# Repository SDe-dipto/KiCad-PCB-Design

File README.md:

# KiCad-PCB-Design
This repository contains project designs of PCBs implemented using KiCad tool. 

## Example projects
1. 6SN7 dual triode vacuum tube
2. 10-channel equaliser
3. Circular LED board
4. LM324 operational amplifier-based filter

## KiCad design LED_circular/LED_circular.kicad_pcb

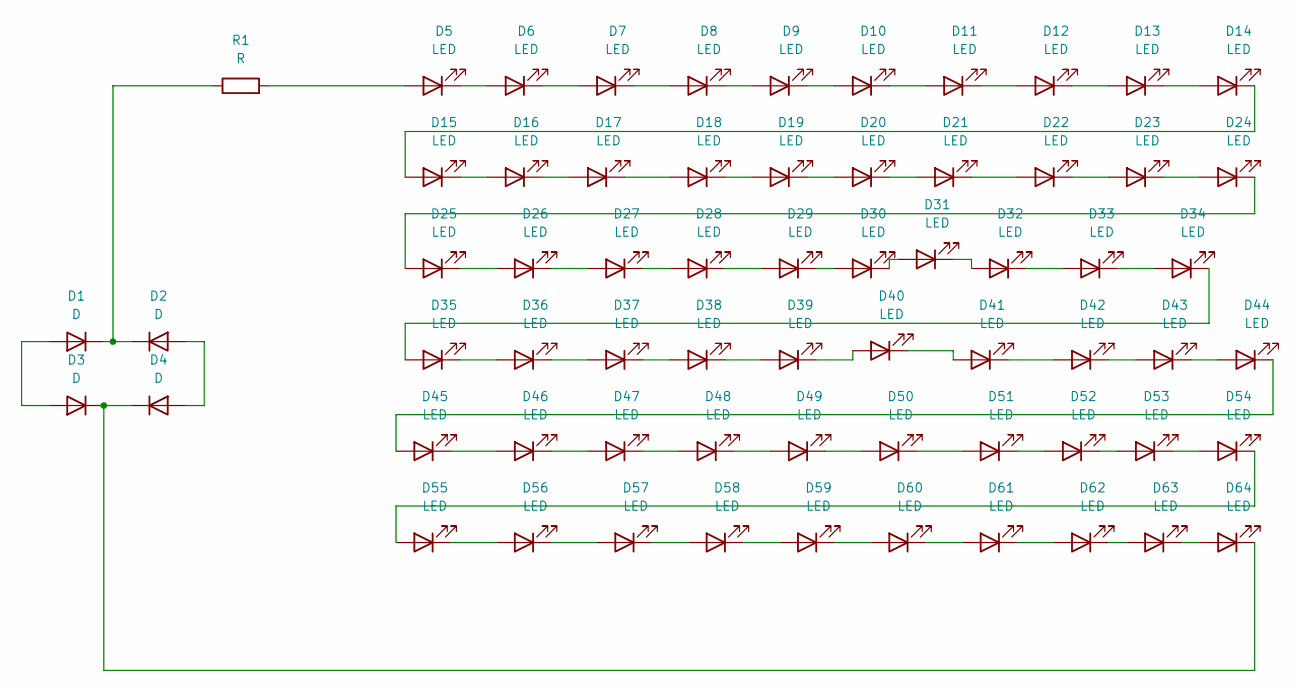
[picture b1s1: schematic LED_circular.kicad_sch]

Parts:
D1, D2, D3, D4: D; D_1206_3216Metric
D5, D6, D7, D8, D9, D10, D11, D12, D13, D14, D15, D16, D17, D18, D19, D20, D21, D22, D23, D24, D25, D26, D27, D28, D29, D30, D31, D32, D33, D34, D35, D36, D37, D38, D39, D40, D41, D42, D43, D44, D45, D46, D47, D48, D49, D50, D51, D52, D53, D54, D55, D56, D57, D58, D59, D60, D61, D62, D63, D64: LED; LED_1206_3216Metric
R1: R; R_1206_3216Metric

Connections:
unnamed: D1.2 (A), D3.2 (A)
unnamed: D1.1 (K), D2.1 (K), R1.1
unnamed: D2.2 (A), D4.2 (A)
unnamed: D3.1 (K), D4.1 (K), D64.1 (K)
unnamed: D5.2 (A), R1.2
unnamed: D5.1 (K), D6.2 (A)
unnamed: D6.1 (K), D7.2 (A)
unnamed: D7.1 (K), D8.2 (A)
unnamed: D8.1 (K), D9.2 (A)
unnamed: D9.1 (K), D10.2 (A)
unnamed: D10.1 (K), D11.2 (A)
unnamed: D11.1 (K), D12.2 (A)
unnamed: D12.1 (K), D13.2 (A)
unnamed: D13.1 (K), D14.2 (A)
unnamed: D14.1 (K), D15.2 (A)
unnamed: D15.1 (K), D16.2 (A)
unnamed: D16.1 (K), D17.2 (A)
unnamed: D17.1 (K), D18.2 (A)
unnamed: D18.1 (K), D19.2 (A)
unnamed: D19.1 (K), D20.2 (A)
unnamed: D20.1 (K), D21.2 (A)
unnamed: D21.1 (K), D22.2 (A)
unnamed: D22.1 (K), D23.2 (A)
unnamed: D23.1 (K), D24.2 (A)
unnamed: D24.1 (K), D25.2 (A)
unnamed: D25.1 (K), D26.2 (A)
unnamed: D26.1 (K), D27.2 (A)
unnamed: D27.1 (K), D28.2 (A)
unnamed: D28.1 (K), D29.2 (A)
unnamed: D29.1 (K), D30.2 (A)
unnamed: D30.1 (K), D31.2 (A)
unnamed: D31.1 (K), D32.2 (A)
unnamed: D32.1 (K), D33.2 (A)
unnamed: D33.1 (K), D34.2 (A)
unnamed: D34.1 (K), D35.2 (A)
unnamed: D35.1 (K), D36.2 (A)
unnamed: D36.1 (K), D37.2 (A)
unnamed: D37.1 (K), D38.2 (A)
unnamed: D38.1 (K), D39.2 (A)
unnamed: D39.1 (K), D40.2 (A)
unnamed: D40.1 (K), D41.2 (A)
unnamed: D41.1 (K), D42.2 (A)
unnamed: D42.1 (K), D43.2 (A)
unnamed: D43.1 (K), D44.2 (A)
unnamed: D44.1 (K), D45.2 (A)
unnamed: D45.1 (K), D46.2 (A)
unnamed: D46.1 (K), D47.2 (A)
unnamed: D47.1 (K), D48.2 (A)
unnamed: D48.1 (K), D49.2 (A)
unnamed: D49.1 (K), D50.2 (A)
unnamed: D50.1 (K), D51.2 (A)
unnamed: D51.1 (K), D52.2 (A)
unnamed: D52.1 (K), D53.2 (A)
unnamed: D53.1 (K), D54.2 (A)
unnamed: D54.1 (K), D55.2 (A)
unnamed: D55.1 (K), D56.2 (A)
unnamed: D56.1 (K), D57.2 (A)
unnamed: D57.1 (K), D58.2 (A)
unnamed: D58.1 (K), D59.2 (A)
unnamed: D59.1 (K), D60.2 (A)
unnamed: D60.1 (K), D61.2 (A)
unnamed: D61.1 (K), D62.2 (A)
unnamed: D62.1 (K), D63.2 (A)
unnamed: D63.1 (K), D64.2 (A)

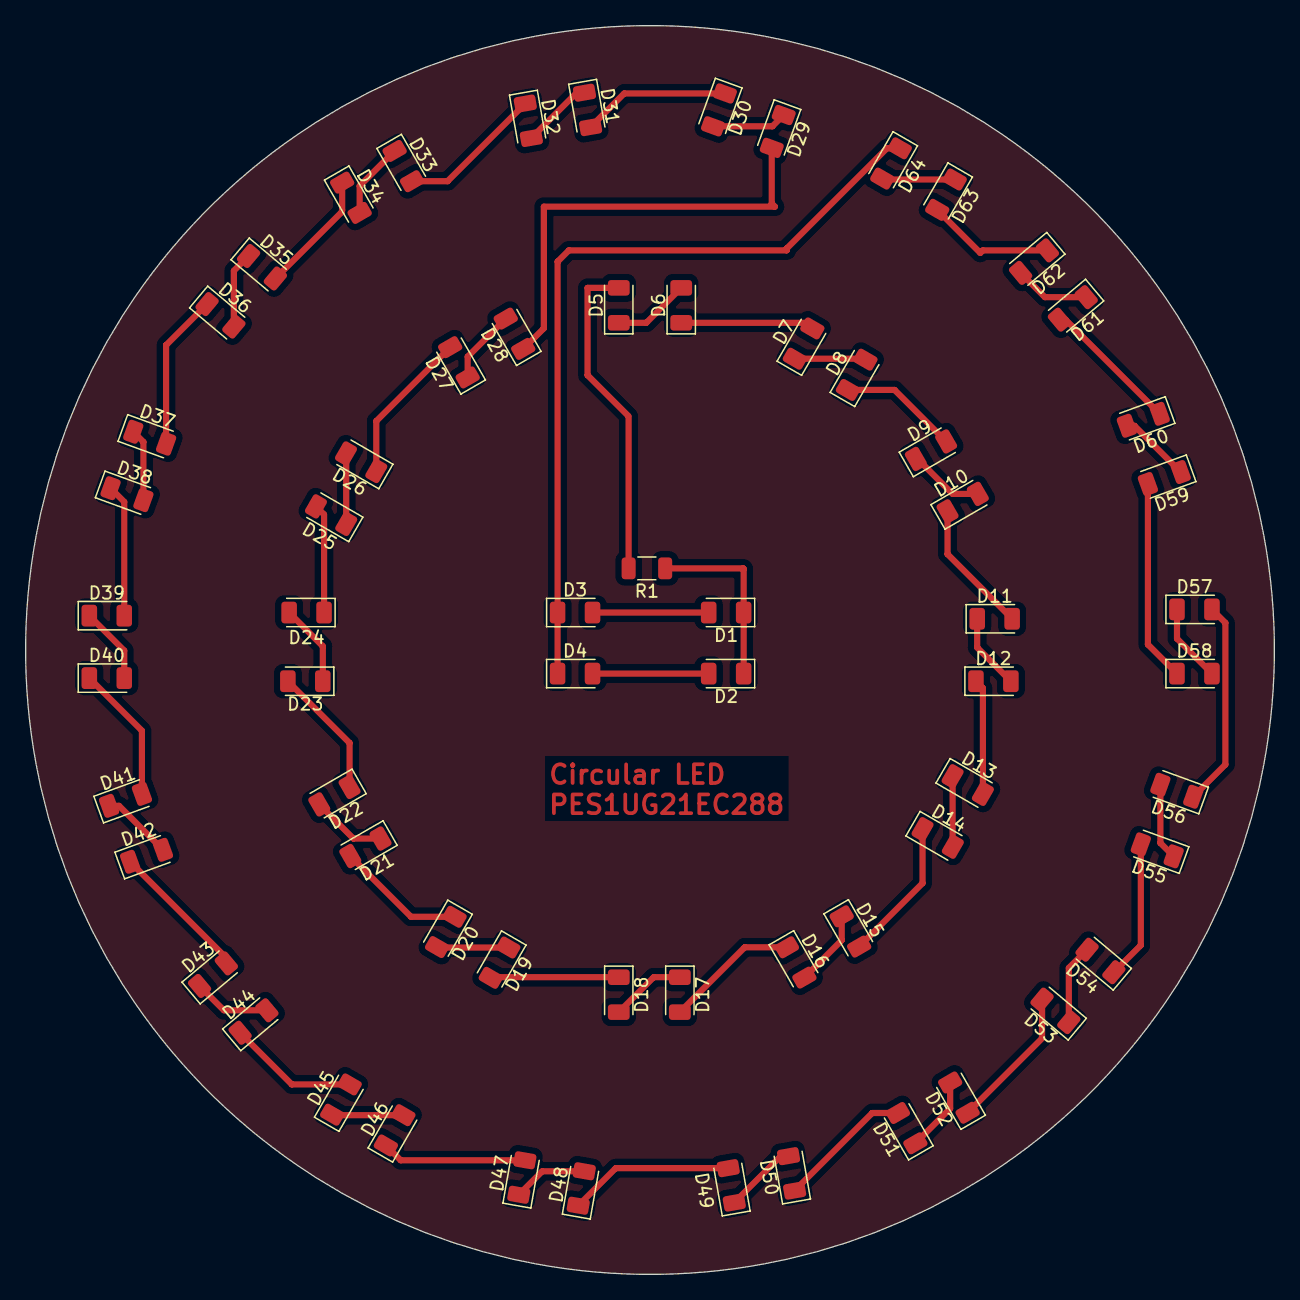
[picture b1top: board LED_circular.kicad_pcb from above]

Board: 2 copper layers, 100.0 x 100.0 mm, 65 parts (0 on the bottom side), 64 nets.

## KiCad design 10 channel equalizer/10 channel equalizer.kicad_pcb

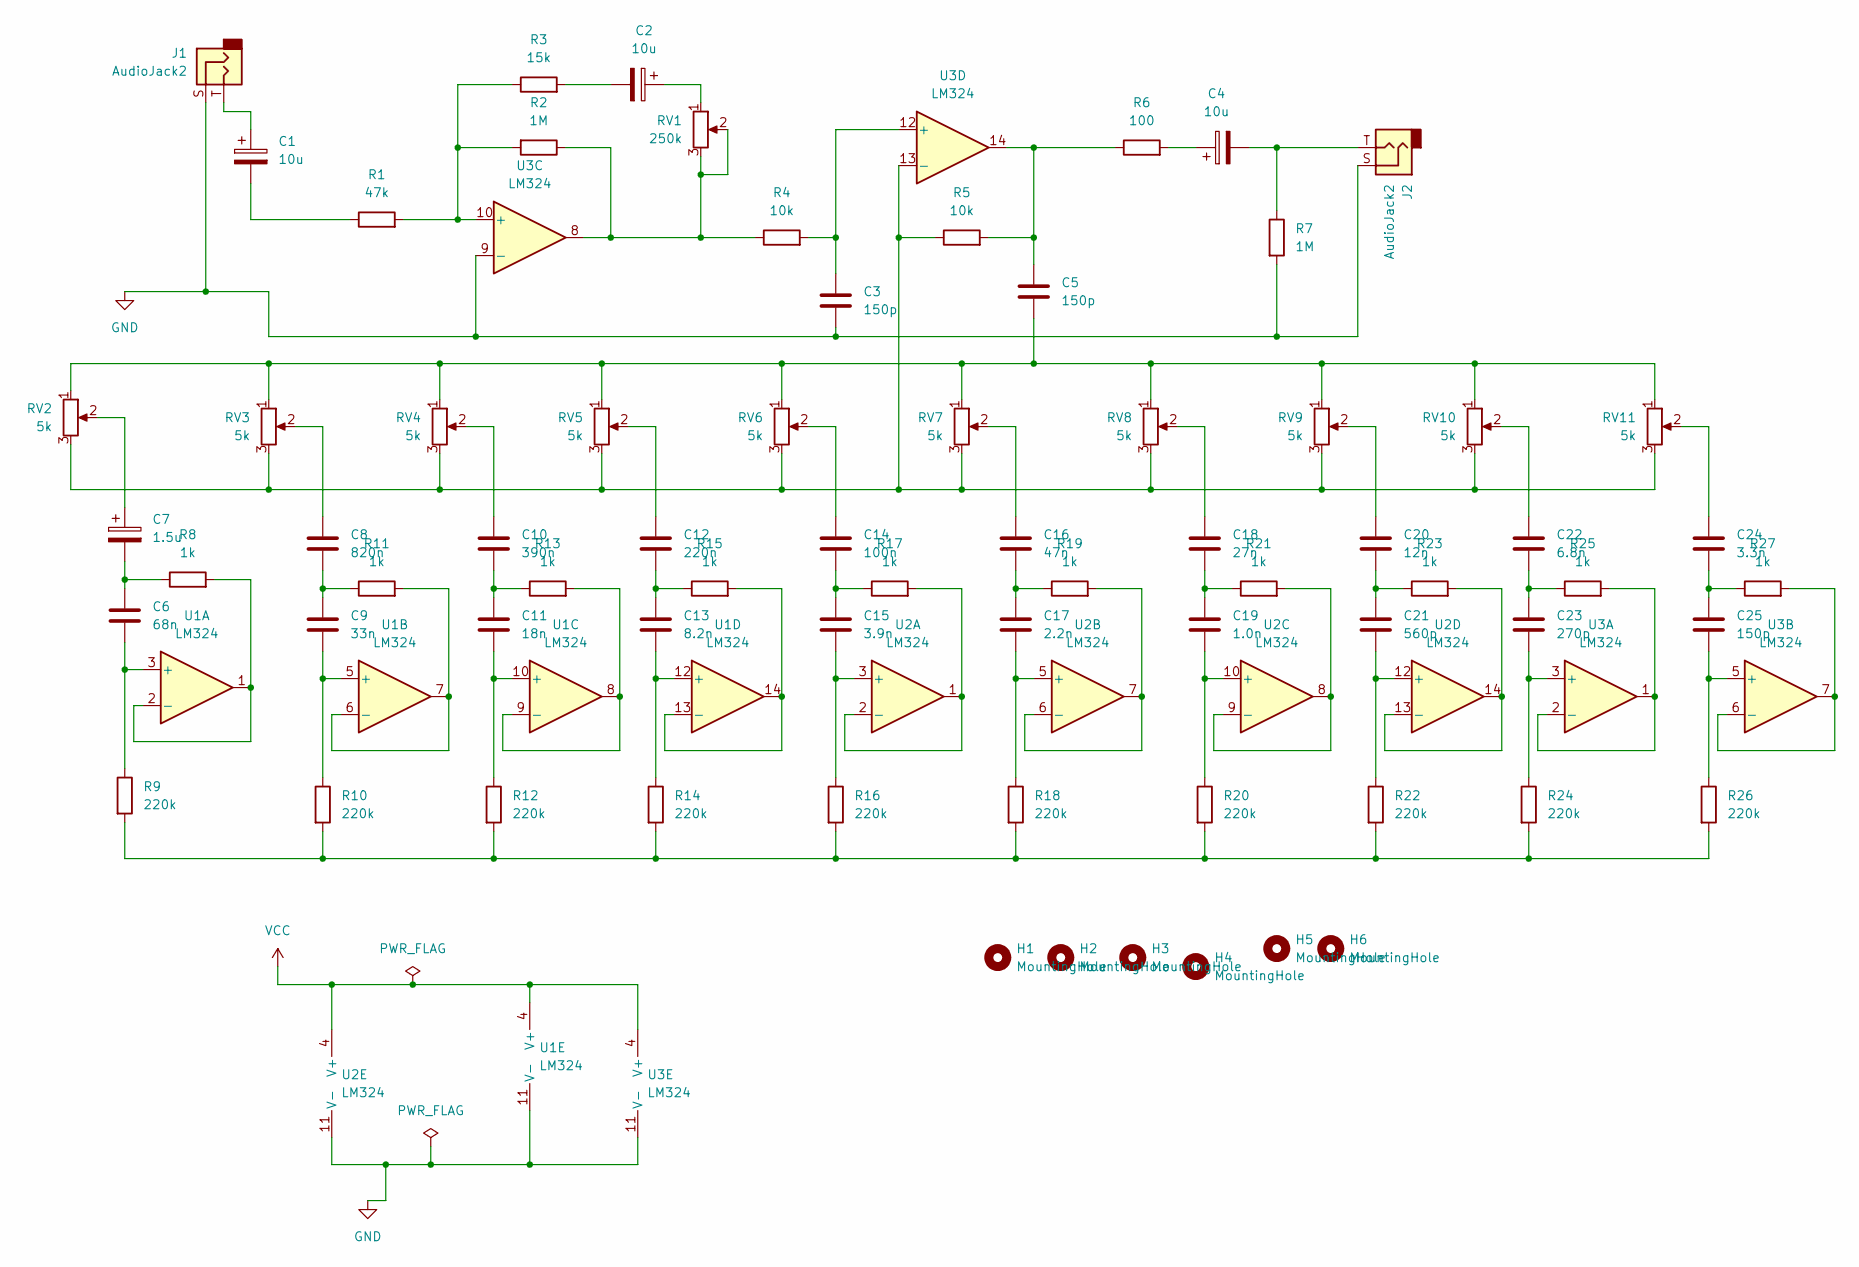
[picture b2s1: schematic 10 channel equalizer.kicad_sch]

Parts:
C1, C2, C4: 10u; C_1206_3216Metric
C3, C5, C25: 150p; C_1206_3216Metric
C6: 68n; C_1206_3216Metric
C7: 1.5u; C_1206_3216Metric
C8: 820n; C_1206_3216Metric
C9: 33n; C_1206_3216Metric
C10: 390n; C_1206_3216Metric
C11: 18n; C_1206_3216Metric
C12: 220n; C_1206_3216Metric
C13: 8.2n; C_1206_3216Metric
C14: 100n; C_1206_3216Metric
C15: 3.9n; C_1206_3216Metric
C16: 47n; C_1206_3216Metric
C17: 2.2n; C_1206_3216Metric
C18: 27n; C_1206_3216Metric
C19: 1.0n; C_1206_3216Metric
C20: 12n; C_1206_3216Metric
C21: 560p; C_1206_3216Metric
C22: 6.8n; C_1206_3216Metric
C23: 270p; C_1206_3216Metric
C24: 3.3n; C_1206_3216Metric
H1, H2, H3, H4, H5, H6: MountingHole; MountingHole_3.5mm
J1, J2: AudioJack2; Jack_3.5mm_CUI_SJ-3523-SMT_Horizontal
R1: 47k; R_1206_3216Metric
R2, R7: 1M; R_1206_3216Metric
R3: 15k; R_1206_3216Metric
R4, R5: 10k; R_1206_3216Metric
R6: 100; R_1206_3216Metric
R8, R11, R13, R15, R17, R19, R21, R23, R25, R27: 1k; R_1206_3216Metric
R9, R10, R12, R14, R16, R18, R20, R22, R24, R26: 220k; R_1206_3216Metric
RV1: 250k; Potentiometer_Bourns_PTA6043_Single_Slide
RV2, RV3, RV4, RV5, RV6, RV7, RV8, RV9, RV10, RV11: 5k; Potentiometer_Bourns_PTA6043_Single_Slide
U1, U2, U3: LM324; SOIC-14_3.9x8.7mm_P1.27mm

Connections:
GND: C3.2, J1.S, J2.S, R7.2, U1.11 (V-), U2.11 (V-), U3.9 (-), U3.11 (V-)
unnamed: C1.1, J1.T
unnamed: C1.2, R1.1
unnamed: C2.1, RV1.1
unnamed: C2.2, R3.2
unnamed: C4.1, R6.2
unnamed: C4.2, J2.T, R7.1
unnamed: C5.1, R5.2, R6.1, U3.14
unnamed: C5.2, RV2.1, RV3.1, RV4.1, RV5.1, RV6.1, RV7.1, RV8.1, RV9.1, RV10.1, RV11.1
unnamed: C6.1, C7.2, R8.1
unnamed: C7.1, RV2.2
unnamed: C8.1, RV3.2
unnamed: C8.2, C9.1, R11.1
unnamed: C10.1, RV4.2
unnamed: C10.2, C11.1, R13.1
unnamed: C12.1, RV5.2
unnamed: C12.2, C13.1, R15.1
unnamed: C14.1, RV6.2
unnamed: C14.2, C15.1, R17.1
unnamed: C16.1, RV7.2
unnamed: C16.2, C17.1, R19.1
unnamed: C18.1, RV8.2
unnamed: C18.2, C19.1, R21.1
unnamed: C20.1, RV9.2
unnamed: C20.2, C21.1, R23.1
unnamed: C22.1, RV10.2
unnamed: C22.2, C23.1, R25.1
unnamed: C24.1, RV11.2
unnamed: C24.2, C25.1, R27.1
unnamed: R2.1, R4.1, RV1.2, RV1.3, U3.8
unnamed: R9.2, R10.2, R12.2, R14.2, R16.2, R18.2, R20.2, R22.2, R24.2, R26.2
unnamed: C6.2, R9.1, U1.3 (+)
unnamed: R8.2, U1.1, U1.2 (-)
unnamed: C9.2, R10.1, U1.5 (+)
unnamed: R11.2, U1.6 (-), U1.7
unnamed: C11.2, R12.1, U1.10 (+)
unnamed: R13.2, U1.8, U1.9 (-)
unnamed: C13.2, R14.1, U1.12 (+)
unnamed: R15.2, U1.13 (-), U1.14
unnamed: C15.2, R16.1, U2.3 (+)
unnamed: R17.2, U2.1, U2.2 (-)
unnamed: C17.2, R18.1, U2.5 (+)
unnamed: R19.2, U2.6 (-), U2.7
unnamed: C19.2, R20.1, U2.10 (+)
unnamed: R21.2, U2.8, U2.9 (-)
unnamed: C21.2, R22.1, U2.12 (+)
unnamed: R23.2, U2.13 (-), U2.14
unnamed: C23.2, R24.1, U3.3 (+)
unnamed: R25.2, U3.1, U3.2 (-)
unnamed: C25.2, R26.1, U3.5 (+)
unnamed: R27.2, U3.6 (-), U3.7
unnamed: R1.2, R2.2, R3.1, U3.10 (+)
unnamed: C3.1, R4.2, U3.12 (+)
unnamed: R5.1, RV2.3, RV3.3, RV4.3, RV5.3, RV6.3, RV7.3, RV8.3, RV9.3, RV10.3, RV11.3, U3.13 (-)
VCC: U1.4 (V+), U2.4 (V+), U3.4 (V+)

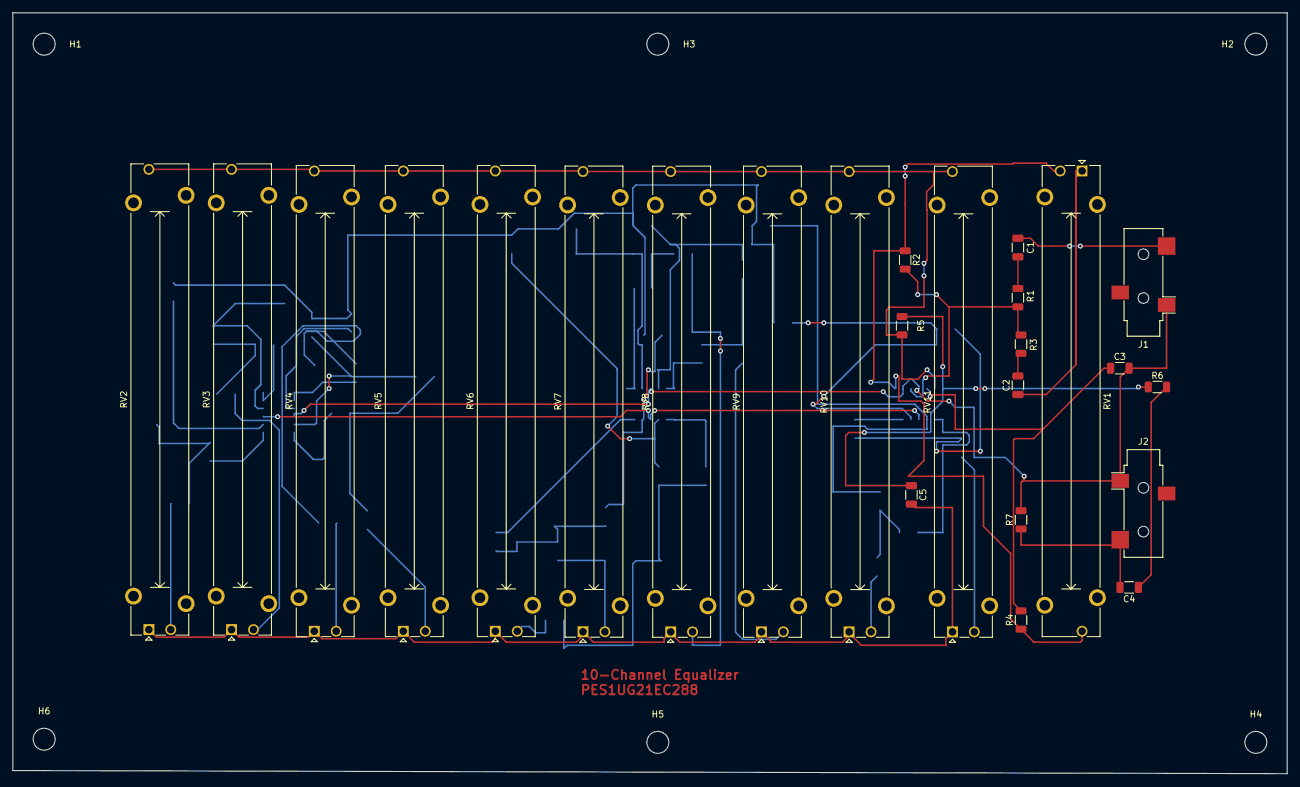
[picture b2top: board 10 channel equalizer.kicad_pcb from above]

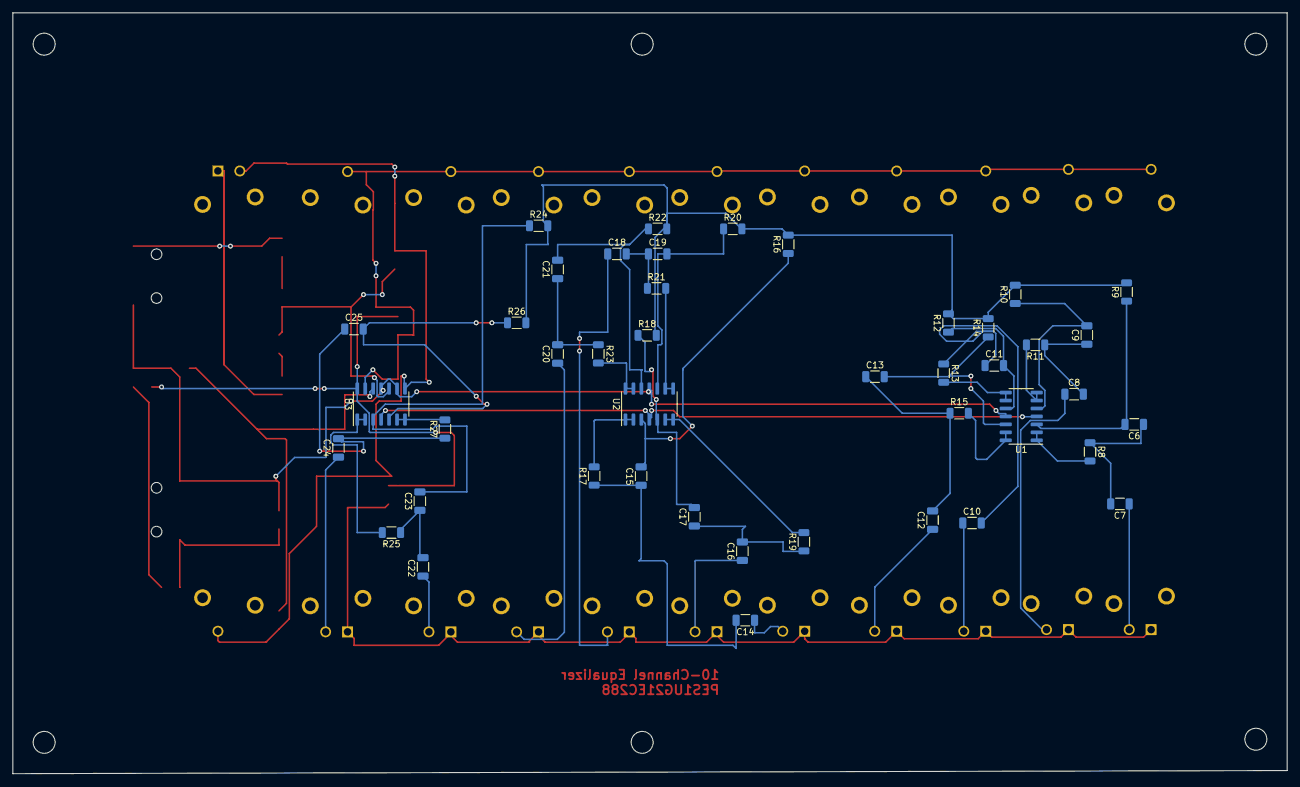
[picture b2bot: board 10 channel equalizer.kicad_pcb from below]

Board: 2 copper layers, 203.5 x 121.5 mm, 74 parts (43 on the bottom side), 55 nets.

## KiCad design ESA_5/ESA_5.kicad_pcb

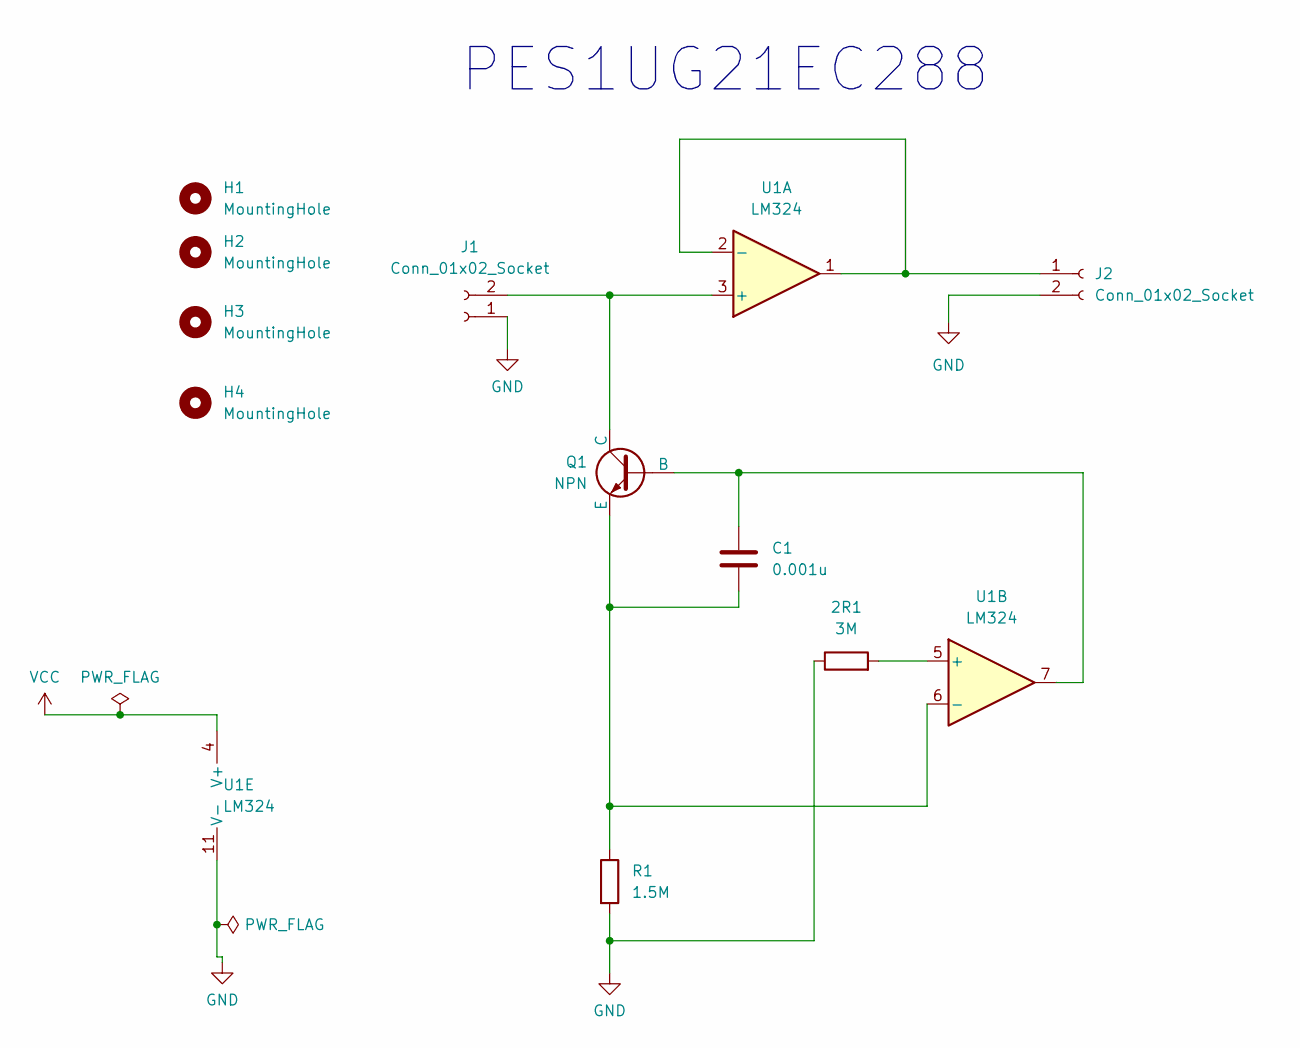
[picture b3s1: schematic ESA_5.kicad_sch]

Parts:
2R1: 3M; R_Axial_DIN0207_L6.3mm_D2.5mm_P2.54mm_Vertical
C1: 0.001u; CP_Axial_L10.0mm_D4.5mm_P15.00mm_Horizontal
H1, H2, H3, H4: MountingHole; MountingHole_3.5mm
J1, J2: Conn_01x02_Socket; PinHeader_1x02_P2.54mm_Horizontal
Q1: NPN; TO-18-3
R1: 1.5M; R_Axial_DIN0207_L6.3mm_D2.5mm_P2.54mm_Vertical
U1: LM324; DIP-14_W7.62mm

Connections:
GND: 2R1.1, J1.1, J2.2, R1.2, U1.11 (V-)
unnamed: J1.2, Q1.1 (C), U1.3 (+)
unnamed: J2.1, U1.1, U1.2 (-)
unnamed: C1.1, Q1.2 (B), U1.7
unnamed: C1.2, Q1.3 (E), R1.1, U1.6 (-)
unnamed: 2R1.2, U1.5 (+)
VCC: U1.4 (V+)

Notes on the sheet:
PES1UG21EC288

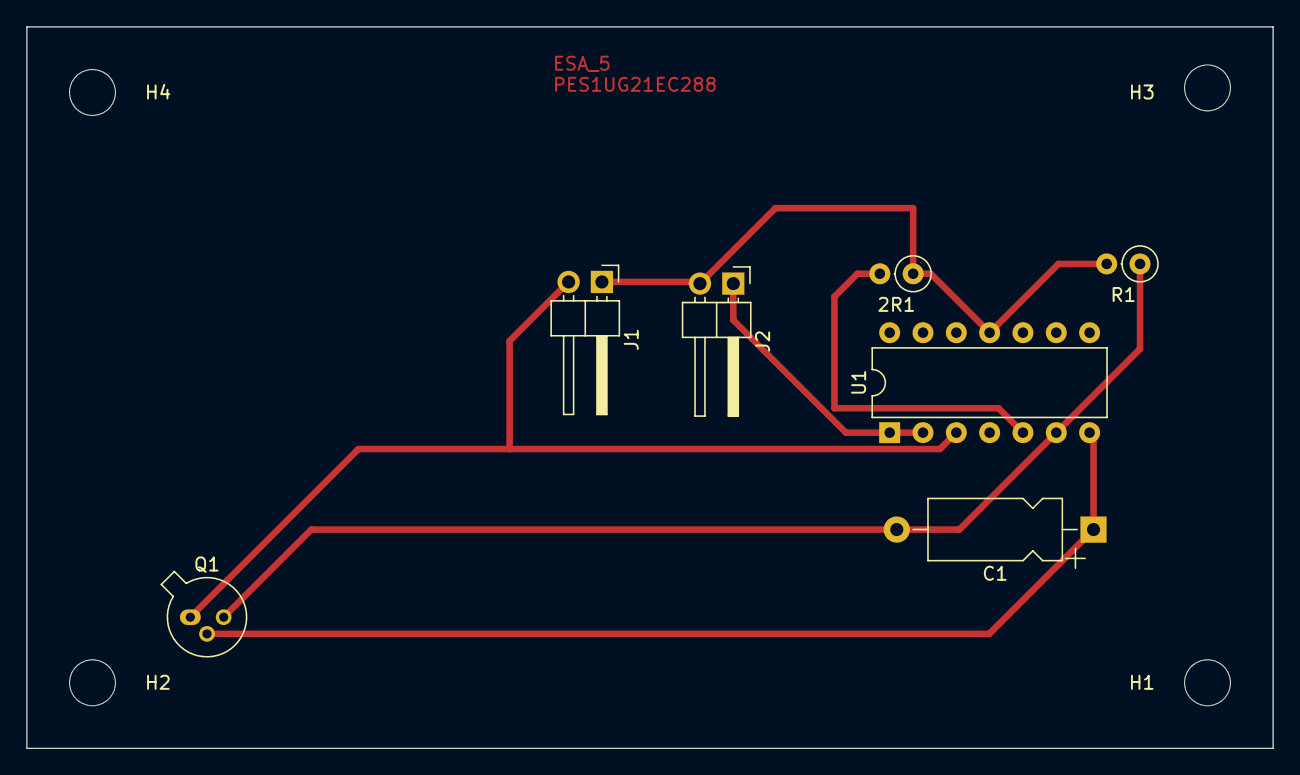
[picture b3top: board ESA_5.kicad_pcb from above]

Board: 2 copper layers, 95.0 x 55.0 mm, 11 parts (0 on the bottom side), 6 nets.

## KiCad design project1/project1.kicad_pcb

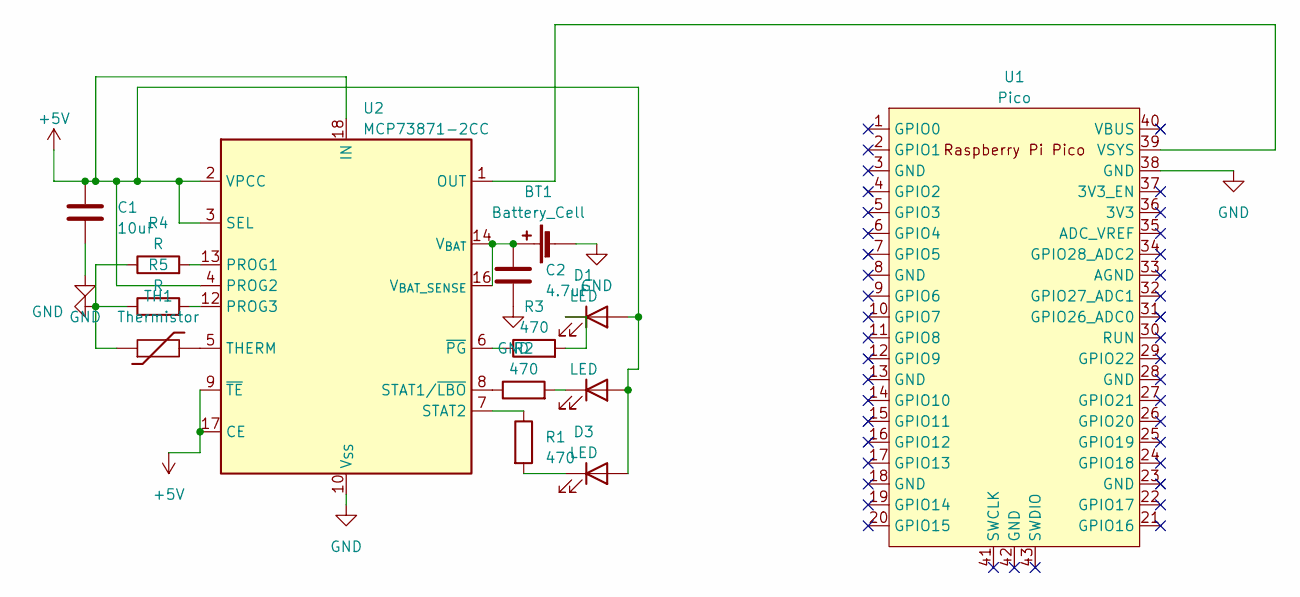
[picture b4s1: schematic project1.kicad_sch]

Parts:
BT1: Battery_Cell; BatteryHolder_Keystone_1042_1x18650
C1: 10uF; C_0402_1005Metric
C2: 4.7uF; C_0402_1005Metric
D1, D2, D3: LED; LED_0402_1005Metric
R1, R2, R3: 470; R_0402_1005Metric
R4, R5: R; R_0402_1005Metric
TH1: Thermistor; R_0402_1005Metric
U1: Pico; RPi_Pico_SMD_TH
U2: MCP73871-2CC; QFN-20-1EP_4x4mm_P0.5mm_EP2.5x2.5mm

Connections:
+5V: C1.1, D1.2 (A), D2.2 (A), D3.2 (A), U2.2 (VPCC), U2.3 (SEL), U2.4 (PROG2), U2.9 (~TE), U2.17 (CE), U2.18 (IN), U2.19 (IN)
GND: BT1.2 (-), C1.2, C2.1, R4.1, R5.1, TH1.1, U1.38 (GND), U2.10 (V_{SS}), U2.11 (V_{SS}), U2.21 (V_{SS})
unnamed: BT1.1 (+), C2.2, U2.14 (V_{BAT}), U2.15 (V_{BAT}), U2.16 (V_{BAT_SENSE})
unnamed: D1.1 (K), R3.2
unnamed: D2.1 (K), R2.2
unnamed: D3.1 (K), R1.2
unnamed: U1.39 (VSYS), U2.1 (OUT), U2.20 (OUT)
unnamed: R4.2, U2.13 (PROG1)
unnamed: R5.2, U2.12 (PROG3)
unnamed: R2.1, U2.8 (STAT1/~LBO)
unnamed: R1.1, U2.7 (STAT2)
unnamed: TH1.2, U2.5 (THERM)
unnamed: R3.1, U2.6 (~PG)

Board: 2 copper layers, 14 parts (0 on the bottom side), 13 nets, no tracks yet.

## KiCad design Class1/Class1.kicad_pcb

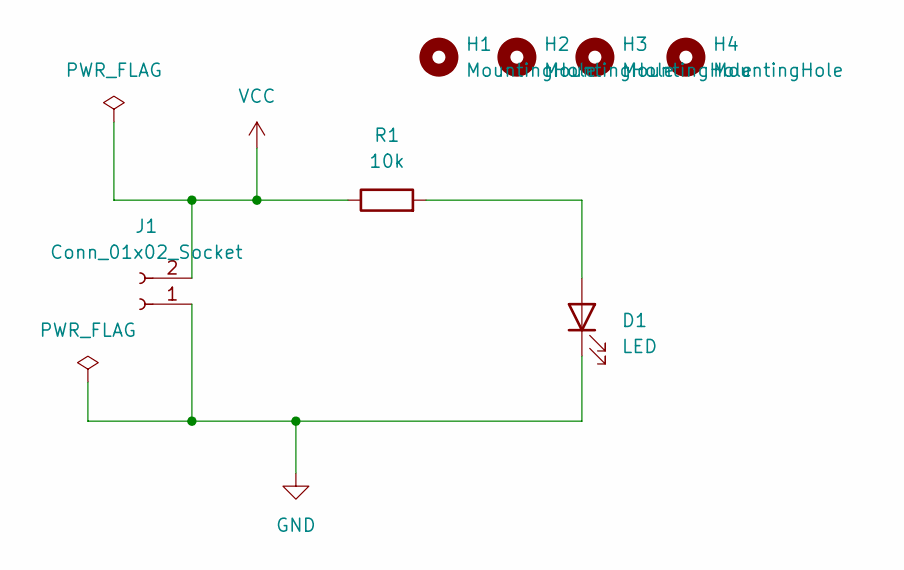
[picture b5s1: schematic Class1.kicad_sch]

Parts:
D1: LED; LED_D5.0mm
H1, H2, H3, H4: MountingHole; MountingHole_3.5mm
J1: Conn_01x02_Socket; PinSocket_1x02_P2.54mm_Vertical
R1: 10k; R_Axial_DIN0207_L6.3mm_D2.5mm_P15.24mm_Horizontal

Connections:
GND: D1.1 (K), J1.1
unnamed: D1.2 (A), R1.2
VCC: J1.2, R1.1

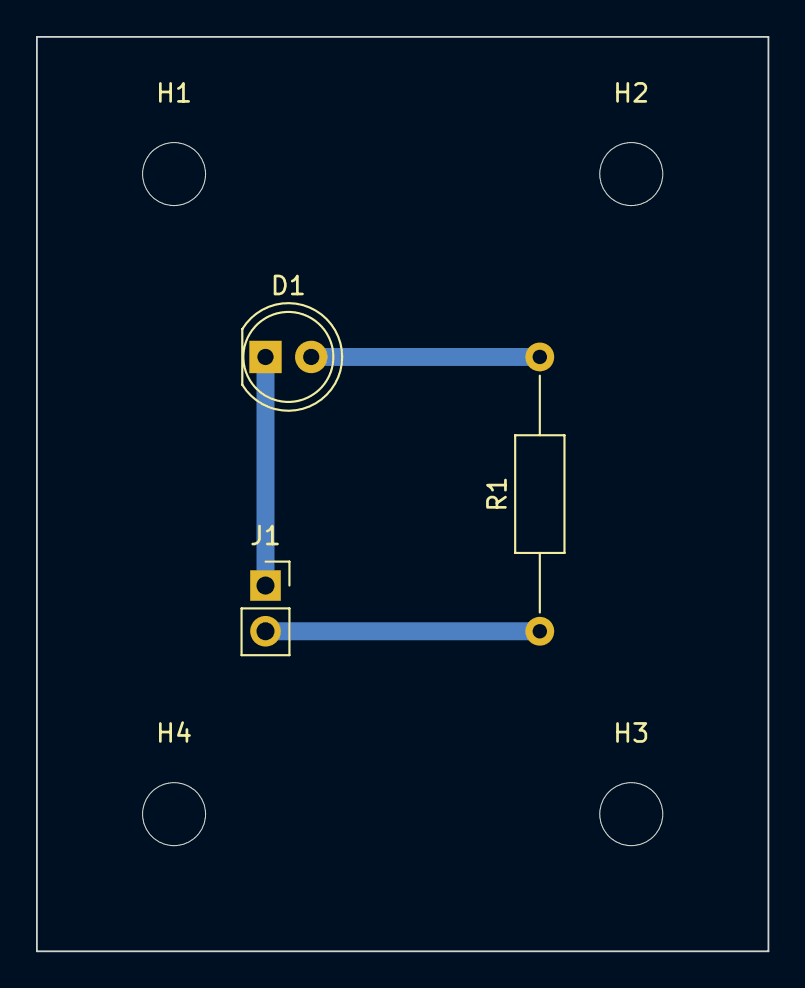
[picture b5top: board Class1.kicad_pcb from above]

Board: 2 copper layers, 40.6 x 50.8 mm, 7 parts (0 on the bottom side), 3 nets.

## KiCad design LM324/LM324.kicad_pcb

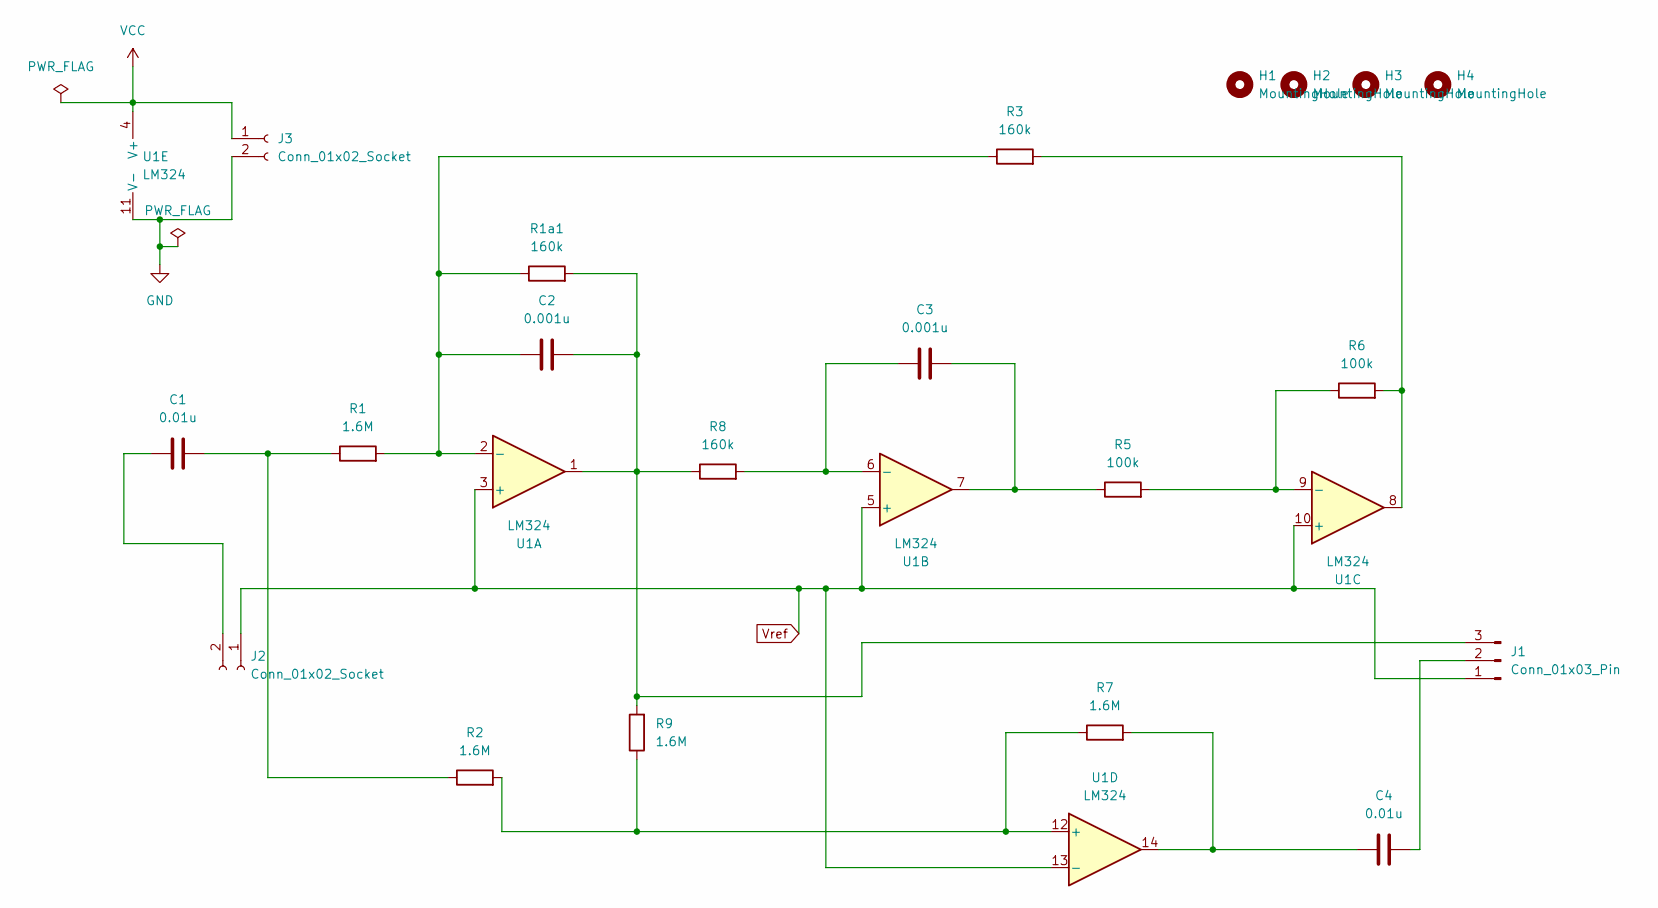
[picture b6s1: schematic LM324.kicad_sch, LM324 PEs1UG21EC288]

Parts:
C1, C4: 0.01u; CP_Axial_L18.0mm_D10.0mm_P25.00mm_Horizontal
C2, C3: 0.001u; CP_Axial_L18.0mm_D10.0mm_P25.00mm_Horizontal
H1: MountingHole; MountingHole_2.5mm
H2, H3, H4: MountingHole; MountingHole_3mm
J1: Conn_01x03_Pin; PinHeader_1x03_P2.54mm_Vertical
J2, J3: Conn_01x02_Socket; PinSocket_1x02_P2.54mm_Vertical
R1, R2, R7, R9: 1.6M; R_Axial_DIN0207_L6.3mm_D2.5mm_P15.24mm_Horizontal
R1a1, R3, R8: 160k; R_Axial_DIN0207_L6.3mm_D2.5mm_P15.24mm_Horizontal
R5, R6: 100k; R_Axial_DIN0207_L6.3mm_D2.5mm_P15.24mm_Horizontal
U1: LM324; DIP-14_W7.62mm

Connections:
GND: J3.2, U1.11 (V-)
unnamed: C1.2, R1.1, R2.1
unnamed: C3.2, R5.1, U1.7
unnamed: C4.1, R7.2, U1.14
unnamed: C4.2, J1.2
unnamed: C2.2, J1.3, R1a1.2, R8.1, R9.2, U1.1
unnamed: C1.1, J2.2
unnamed: R3.2, R6.2, U1.8
unnamed: C2.1, R1.2, R1a1.1, R3.1, U1.2 (-)
unnamed: C3.1, R8.2, U1.6 (-)
unnamed: R5.2, R6.1, U1.9 (-)
unnamed: R2.2, R7.1, R9.1, U1.12 (+)
VCC: J3.1, U1.4 (V+)
Vref: J1.1, J2.1, U1.3 (+), U1.5 (+), U1.10 (+), U1.13 (-)

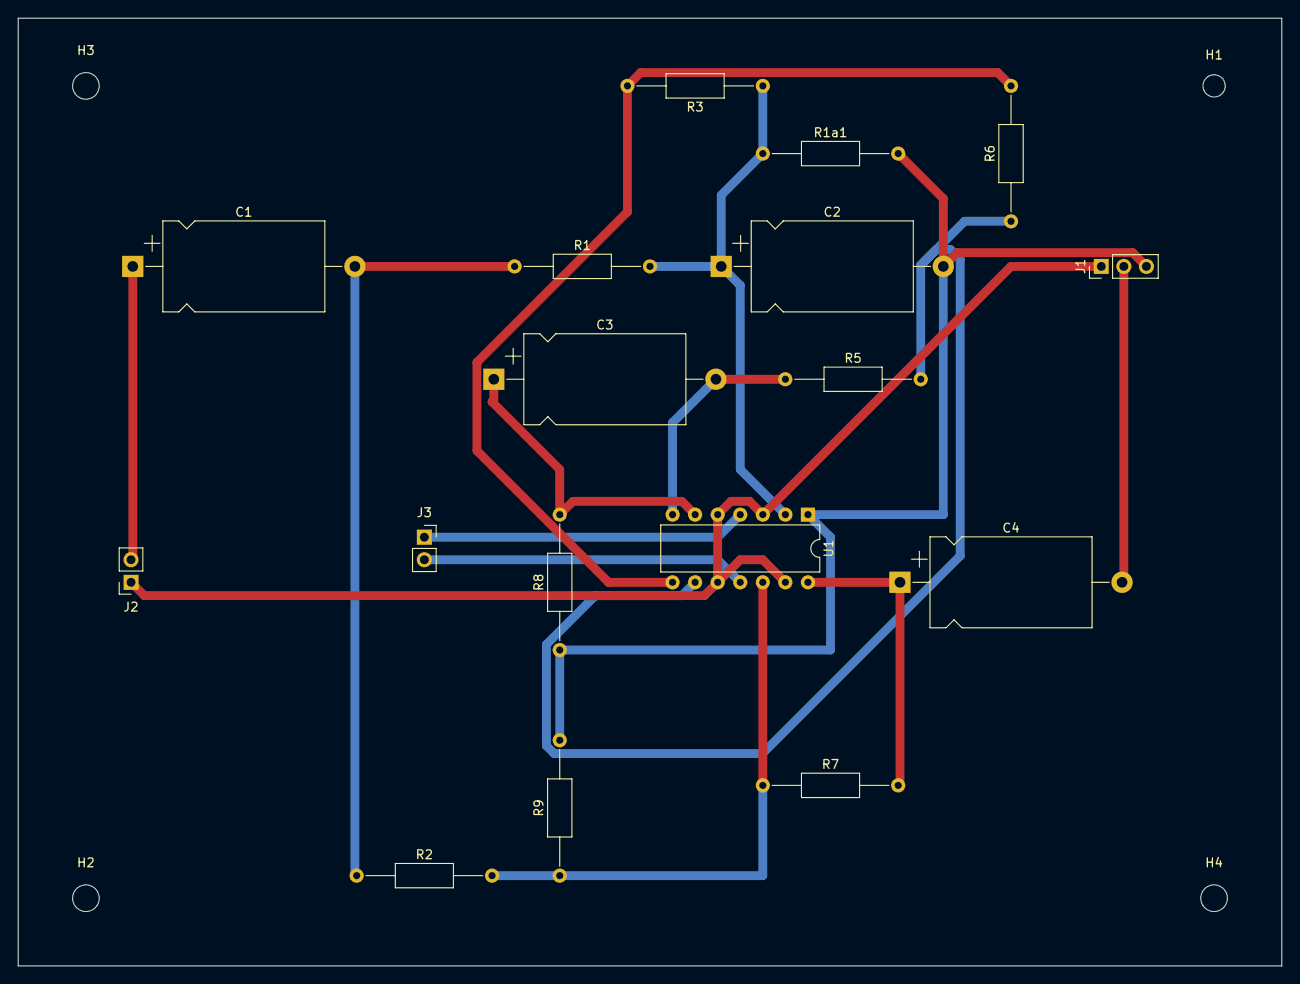
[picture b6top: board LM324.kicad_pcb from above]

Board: 2 copper layers, 142.2 x 106.7 mm, 21 parts (0 on the bottom side), 14 nets.

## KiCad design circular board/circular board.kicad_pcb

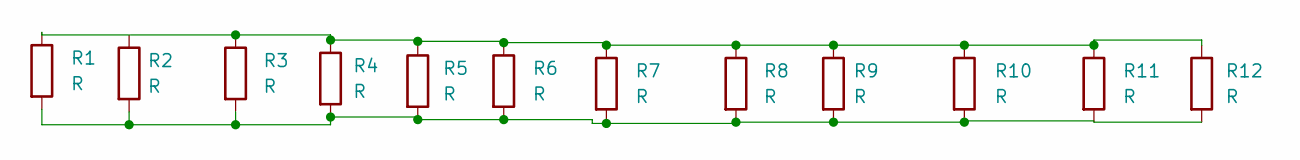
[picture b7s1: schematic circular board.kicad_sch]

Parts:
R1, R2, R3, R4, R5, R6, R7, R8, R9, R10, R11, R12: R; R_Axial_DIN0204_L3.6mm_D1.6mm_P5.08mm_Horizontal

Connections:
unnamed: R1.1, R2.1
unnamed: R1.2, R2.2, R3.2, R4.2, R5.2, R6.2, R7.2, R8.2, R9.2, R10.2
unnamed: R3.1, R4.1, R5.1, R6.1, R7.1, R8.1, R9.1, R10.1, R11.1, R12.1
unnamed: R11.2, R12.2

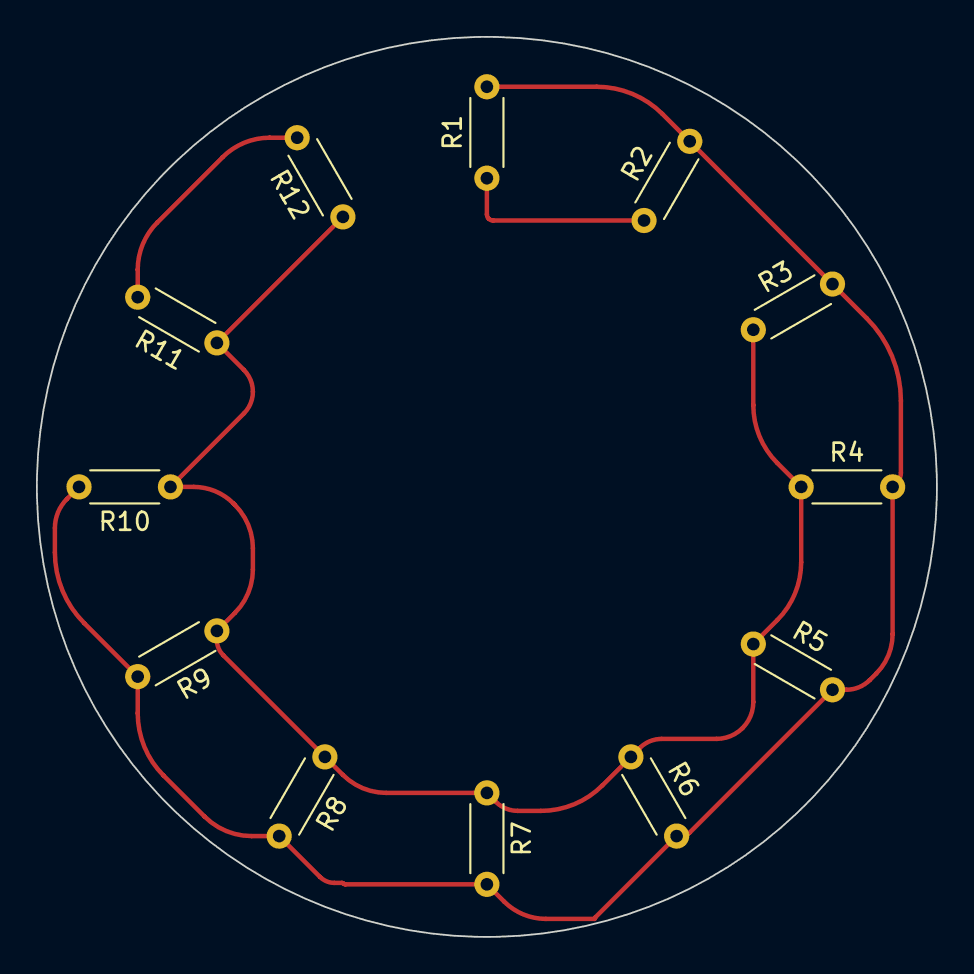
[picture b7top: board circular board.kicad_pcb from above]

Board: 2 copper layers, 50.0 x 50.0 mm, 12 parts (0 on the bottom side), 4 nets.

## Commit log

2025-05-03 pushing Git KiCad projects
